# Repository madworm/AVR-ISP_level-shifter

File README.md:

AVR-ISP_level-shifter
=====================

LAYOUT FILES: Bidirectional level-shifter for old 5V-only AVR-ISP programmers
	      (or for ones that claim to do 3.3V and only offer that on VCC - not on I/O).

---

Before having PC-boards made, please make sure you know about your manufacturer's peculiarities!
Especially drill-sizes and their tolerances may vary too much and give you trouble.

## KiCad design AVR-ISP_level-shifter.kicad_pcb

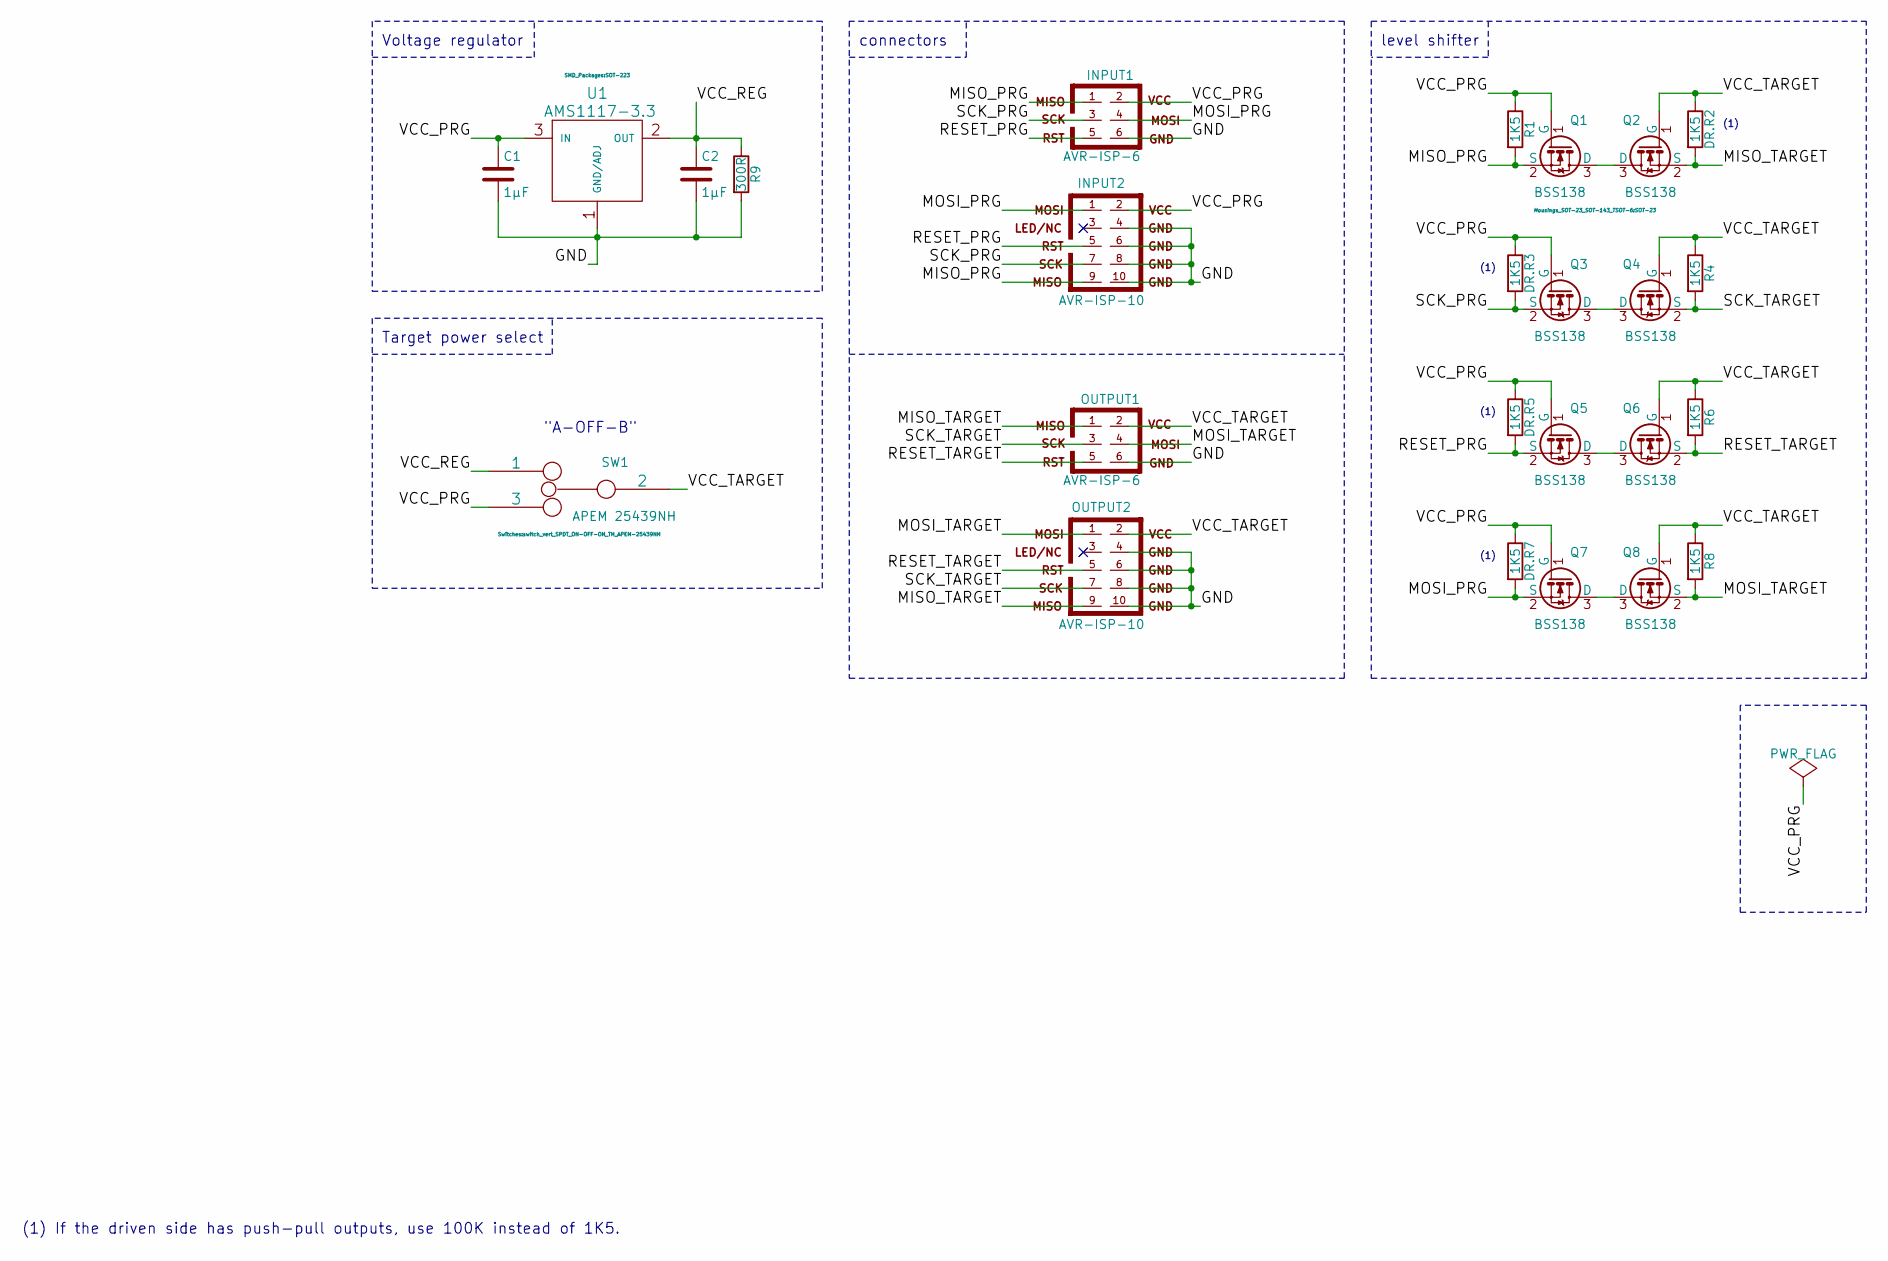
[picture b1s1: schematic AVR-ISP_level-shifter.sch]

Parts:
C1, C2: 1µF; C_0603
DR.R2, DR.R3, DR.R5, DR.R7: 1K5; R_0603
INPUT1: AVR-ISP-6; DIL-3
INPUT2: AVR-ISP-10; DIL-5
OUTPUT1: AVR-ISP-6; DIL-3
OUTPUT2: AVR-ISP-10; DIL-5
Q1, Q2, Q3, Q4, Q5, Q6, Q7, Q8: BSS138; SOT-23
R1, R4, R6, R8: 1K5; R_0603
R9: 300R; R_0603
SW1: APEM 25439NH; switch_vert_SPDT_ON-OFF-ON_TH_APEM-25439NH
U1: AMS1117-3.3; SOT-223

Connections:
/GND: C1.2, C2.2, INPUT1.6, INPUT2.4, INPUT2.6, INPUT2.8, INPUT2.10, OUTPUT1.6, OUTPUT2.4, OUTPUT2.6, OUTPUT2.8, OUTPUT2.10, R9.2, U1.1 (GND/ADJ)
/MISO_PRG: INPUT1.1, INPUT2.9, Q1.2 (S), R1.2
/MISO_TARGET: DR.R2.2, OUTPUT1.1, OUTPUT2.9, Q2.2 (S)
/MOSI_PRG: DR.R7.2, INPUT1.4, INPUT2.1, Q7.2 (S)
/MOSI_TARGET: OUTPUT1.4, OUTPUT2.1, Q8.2 (S), R8.2
/RESET_PRG: DR.R5.2, INPUT1.5, INPUT2.5, Q5.2 (S)
/RESET_TARGET: OUTPUT1.5, OUTPUT2.5, Q6.2 (S), R6.2
/SCK_PRG: DR.R3.2, INPUT1.3, INPUT2.7, Q3.2 (S)
/SCK_TARGET: OUTPUT1.3, OUTPUT2.7, Q4.2 (S), R4.2
/VCC_PRG: C1.1, DR.R3.1, DR.R5.1, DR.R7.1, INPUT1.2, INPUT2.2, Q1.1 (G), Q3.1 (G), Q5.1 (G), Q7.1 (G), R1.1, SW1.3, U1.3 (IN)
/VCC_REG: C2.1, R9.1, SW1.1, U1.2 (OUT)
/VCC_TARGET: DR.R2.1, OUTPUT1.2, OUTPUT2.2, Q2.1 (G), Q4.1 (G), Q6.1 (G), Q8.1 (G), R4.1, R6.1, R8.1, SW1.2
unnamed: Q1.3 (D), Q2.3 (D)
unnamed: Q3.3 (D), Q4.3 (D)
unnamed: Q5.3 (D), Q6.3 (D)
unnamed: Q7.3 (D), Q8.3 (D)

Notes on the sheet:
"A-OFF-B"
connectors
Voltage regulator
Target power select
(1) If the driven side has push-pull outputs, use 100K instead of 1K5.
level shifter
(1)

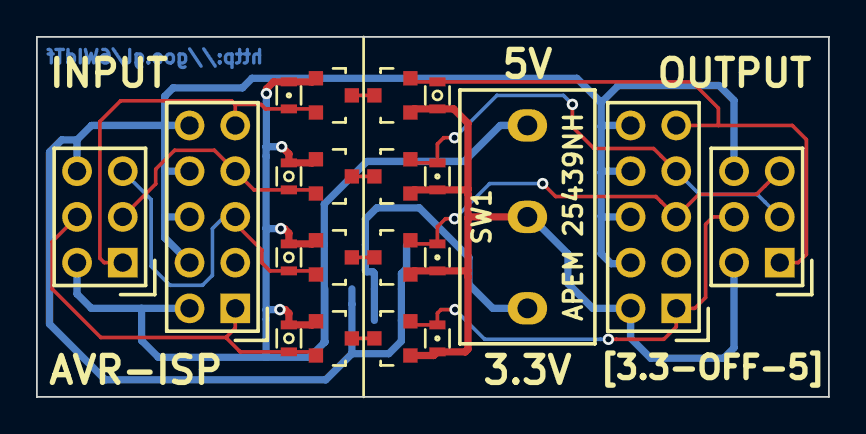
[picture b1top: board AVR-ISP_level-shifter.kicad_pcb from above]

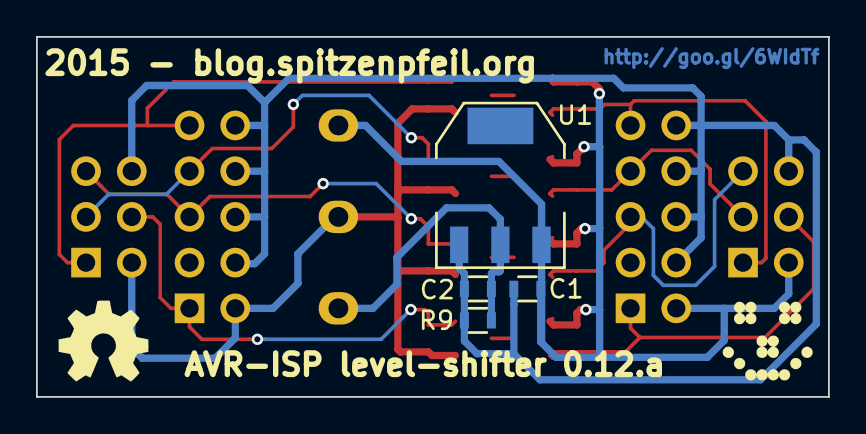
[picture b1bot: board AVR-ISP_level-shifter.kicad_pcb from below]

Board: 2 copper layers, 44.0 x 20.0 mm, 27 parts (6 on the bottom side), 16 nets.

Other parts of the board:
LOGO1: LED_smile_silkscreen_5mm
LOGO2: OSHW-logo_silkscreen_5mm

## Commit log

2015-04-19 Schematic + footprint assignation might be done.
2015-04-19 Changed a few footprints.
2015-04-19 Might be done!
2015-04-19 Tweaks.
2015-04-19 Added shortened URL to github repo to board.
2015-04-19 Updated 'README.md'.
2015-04-24 Added comment to schematic + silkscreen tweaks.
2015-05-05 Added load resistor (~300R) to pull minimum load current out of 3.3V LDO.
2015-05-28 Changed footprints for easier handsoldering + necessary tweaks.
